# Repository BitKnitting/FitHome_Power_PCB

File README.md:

Kicad is used to create the schematic and layout.
# Power PCB
The Power PCB  monitors the voltage and current of a (North American's) home energy lines.  It is the bottom PCB of three PCBs that when combined provide Watt readings and send them over wireless to an mqtt broker.  The other PCBs include:  
* [The meter PCB](https://github.com/BitKnitting/Tisham_PCB_meter_atm90e26).  The meter PCB includes two atm90e26 energy monitor ICs that takes in the analog readings from the power PCB and converts them into DC measurements a microcontroller can read.  
* [The microcontroller PCB](https://github.com/BitKnitting/Tisham_PCB_Feather).  The microcontroller PCB mounts a microcontroller with wifi - like a Feather RFM95 or a wemos D1 (a bit up in the air as of this date - 4/5/2019).  The microcontroller gets the voltage and current readings from the atm90e26's over SPI and then sends them via mqtt.

The three connect together to become the FitHome hardware.

# Thanks to Those That Went Before
This project extends [Tisham Dhar's work on building energy monitors using an atm90e26](https://github.com/whatnick/DIN_Rail_EnergyMonitor).  In particular, [the DIN Rail energy monitor](https://www.crowdsupply.com/whatnick/atm90e26-energy-monitor-kits).  Besides his open source projects, Tisham has been exceptionally helpful and supportive.  Tisham continues to inspire me.  THANK YOU.

Before I took [Chris Gammell's Contextual Electronics course](https://contextualelectronics.com/), I had absolutely no experience with electronics or building PCBs.  Chris is exceptional in so many ways.  THANK YOU.

There is an exceptional community behind [the OpenEnergyMonitor project](https://learn.openenergymonitor.org/).  They not only provide energy monitoring solutions, but are a wealth of knowledge.  THANK YOU.  In particular, thanks to the kindly delivered advice and help from Robert Wall.  THANK YOU, THANK YOU.

# Background Info
 ## Electricity Coming Into Our Homes
 In our North American homes, 120V of electricity comes in through two power lines (L0 and L1).  A third line (N) acts as the reference point (analog ground) for voltage/current measurements.
 
 _Image from [here](https://learn.openenergymonitor.org/electricity-monitoring/ac-power-theory/use-in-north-america)_  

 See the section in the schematic labelled _Incoming 120V_.  
 ### Surges
 The MOVs(Metal Oxide Varistors - RV1, RV2, and RV3 on the schematic) clamp down on the voltage coming in when there are power surges.  Most of the time, voltage in North American homes oscillates from 0 to a peak voltage of 169 volts.  Sometimes this oscillation is disturbed by a spike in voltage caused by a lightning strike or  switching in the power grid:  
   
 # Voltage Sampling
 The Open Energy Monitor project has [great info](https://learn.openenergymonitor.org/electricity-monitoring/voltage-sensing/measuring-voltage-with-an-acac-power-adapter) on the how and the what of voltage sampling.  See the Voltage Sampling section of the schematic.

 Four resistors are run in series to ensure if any one of the resistors breaks down, the full 120V won’t be sent to the rest of the circuit.  Also, the resistors are rated to handle the incoming voltage (in my case 120V…but to be safe probably 240V rated resistors are a better thing to use). 
 
Noted in the atm90e26's datasheet: The pins that are for voltage sampling (15 and 16): _…are differential inputs for voltage. Input range is 120μVrms~600mVrms…_ 

Looking at the voltage divider formula:
  
```
R1 = 220K * 4 = 880K
R2 = 1K
Vin = 120V
Vout = 120(1/881)= 136mV.  
```  
# DC Power 
The atm90e26's and the microcontrollers need 3.3V DC power to work.  Since we have 120V coming in, we can transform it to provide the 3.3V DC power.  See the 120VAC -> 5 and 3.3VDC section in the schematic.  There are three pieces to the conversion:  
* The 120VAC -> 5VDC [SMPS](https://en.wikipedia.org/wiki/Switched-mode_power_supply).  
* The two LDOs.  The signal coming out of the SMPS is too noisy.  The LDOs clean up the signal.  
* The DC-DC isolator. This isolates the power for the atm90e26s from the power for the microcontroller.
# Current Sampling
See the Current Sampling section of the Kicad schematic.
## Current Transformers
 Two Current Transformers (CTs) are needed to get current readings on the two 120V lines.   
   
 ### SCT-013-000 CT
  This CT is the [YHDC SCT-013-000 Current Transformer](https://learn.openenergymonitor.org/electricity-monitoring/ct-sensors/yhdc-sct-013-000-ct-sensor-report).  It is popular with DIY home energy monitors.  There are two numbers of interest in the [YHDC SCT-013-000 datasheet](http://statics3.seeedstudio.com/assets/file/bazaar/product/101990029-SCT-013-000-Datasheet.pdf):    
* The diameter of the clamp opening - 13 mm  
* The I(OUT) - 50 mA  
As Robert Wall of [the Open Energy Monitor project](https://openenergymonitor.org/) noted to me _...the manufacturer will tweak the number of secondary turns to give the best accuracy overall.  The ratio of a c.t. is __ALWAYS__ specified as a ratio of two currents, the rated primary current to the corresponding secondary current. So your SCT-013-000 is __100 A : 50 mA__._  
#### TRS 3.5 Jack
 The CTs use a [TRS 3.5mm audio jack](https://www.cui.com/product/resource/sj-352x-smt-series.pdf) as the connector.  The [SCT-013-000 datasheet][YHDC SCT-013-000 datasheet](http://statics3.seeedstudio.com/assets/file/bazaar/product/101990029-SCT-013-000-Datasheet.pdf) shows how the sleeve and tip of the TRS jack are wired.    

Output k is at the tip.  Output l as at the sleeve.

Also note the zener diode.  This is great to have in the circuit to prevent deadly voltage when the CT is clamped to a live line but the jack is not plugged into the rest of the circuit containing the burden resistor.
#### Tea Kettle Example
_PLEASE NOTE: Most people would advise against do this.  The clamp exposes an open current source.  Thanks to the zener diode, this is not as dangerous as it seems.  That is assuming there really IS a zener diode and it is working..._  

To clarify the workings of this CT, I measured the current used by our tea kettle.    
  
I plugged the kettle into my power cord extender that I made to separate out the live line of the power cord so that I could clamp on the CT.  The black probe of the DMM is touching the sleeve of the CT's jack.  The red probe is touching the tip.  Setting the DMM to measure AC mA, I get a reading of 5.9mA.  
```
V = 120V
I = 5.9mA * 100A / 50mA = .0059*100/.05 = 11.8A
P = IV = 11.8 * 120 = 1,416w
```
Ah!  The power of the tea kettle!  More like it takes alot of energy to boil water for tea.

## Clamping On 
   
 One CT is clamped onto the L0 line.  The other is clamped onto the L1 line.  Because the CT clamps onto the line, you might hear a CT refered to as a current clamp.  

 ## Characteristics of the CT
 The characteristics of a CT to be considered when sourcing include:
 * The amount of Amp Service.  [From this article _Understanding Your Home's Electrical Load_](https://www.bhg.com/home-improvement/electrical/how-to-check-your-homes-electrical-capacity/) _Different homes need different amp services. A 60-amp service is probably inadequate for a modern home. A 100-amp service is good for a home of less than 3,000 square feet that does not have central air-conditioning or electric heat. A home larger than 2,000 square feet that has central air-conditioning or electric heat probably needs a 200-amp service._  According to [Bill Thompson of the Open Energy Monitor Project](https://community.openenergymonitor.org/t/ct-hole-diameter-for-north-america/5149), _US homes built before the late 60s were wired with Copper and typically had 100 Amp service, which used AWG 0 copper...Sometime in the late 60s to early 70s, Copper Service Entrance Wires were replaced by Aluminum. Since Aluminum has more resistance per foot than Copper, the equivalent Aluminum wire is two gauges larger than its Copper counterpart. About that same time, 200 Amp service became the norm._  
 * The wire gauge.  The Outside Diameter of the wire gauge determines how large the diameter of the CT clamp must be.  As Bill noted, wires could be copper or aluminum, or copper-clad aluminum.  More aluminum, more current - the wider the diameter.  
   * [100 Amp Service uses 1/0 AWG](https://community.openenergymonitor.org/t/ct-hole-diameter-for-north-america/5149/3) = [12.08 mm](https://lugsdirect.com/Wire_Insulation_Outside_Diameter_Thickness_600V.html).  
   * 200 Amp Service uses (up to?) 2/0 - 4/0 AWG.  [4/0 AWG has an Outside diameter of 16.04mm](https://lugsdirect.com/Wire_Insulation_Outside_Diameter_Thickness_600V.html).  
* Whether the burden resistor is included.  This design assumes the CT __does not__ include the burden resistor.  I.e.: it's output is a current and not a voltage.  
* The ratio of I(in) : I(out)  
* The inclusion of a zener diode.  This is a terrific safety measure to make sure when the CT is clamped on, there is on open current source.

### The Schematics
The image below shows how the wires of the CT map into the TRS and PCB wiring.  

### 200A CT

The YHD SCT-013-000 can't be used on 200 Amp houses.  The clamp diameter of at least 16.04 mm.  And most likely it is better to have a different coil ratio for the secondary coils.

 ## Taking a Current Reading
 I first learned how the current reading circuit worked by reading [this excellent article on the OpenEnergyMonitor's site](https://learn.openenergymonitor.org/electricity-monitoring/ct-sensors/interface-with-arduino).  If you (like myself) are new to this stuff, it is worth a read.  

 The CT used in this design outputs current.  A "burden resistor" is to convert into a Voltage that can be read by the microcontroller.  To accomodate readings using the ADC of the Arduino as discussed in the project, a DC bias circuit of AREF/2 (2.5V) lifts ADC readings to be between 0 and AREF (5V).
 
 The atm90e26 does not need a DC bias circuit.  
 ### Burden Resistor
 Tisham's design uses a 12R burden resistor.  This is to accomodate the atm90e26's 600mV Vrms input limit.  The OpenEnergyMonitor's article noted the current output's Amplitude is .0707A.  Vpp = 0.0707 x 12 = 848mV.  The amplitude is then 424mV.  The Vrms = 424*sqrt(2) = 600mV.
 
 As Tisham noted: _In recent designs I have been splitting the 12R into 6R-6R and grounding the middle for signal symmetry._  This is why two 5.8R resistors are used.  I ran an LTSpice with:  
 *  a sine wave set at 60Hz with an amplitude of 0.0707A (from the OpenEnergyMonitor's Arduino article)
 * .tran 0 .1 0 .1  

 # Connectors
 Getting connectors right has always been difficult for me.  The connectors used in the Power PCB include:  
 ## J1
 This is a plug in Terminal Block.  It connects the 120V power lines to the power PCB.
 The ones made by Phoenix Connect:  
 The male contact - [PN 1759059](https://media.digikey.com/pdf/Data%20Sheets/Phoenix%20Contact%20PDFs/1759059.pdf) is soldered to the power PCB.
 
 The female contact - [PN 1757051](https://media.digikey.com/pdf/Data%20Sheets/Phoenix%20Contact%20PDFs/1757051.pdf) plugs into the male contact and screws the wires into one of the 6 positions.  

 The prices for one of these connectors was WAY TOO HIGH. It appears there is a "clone" version that costs far less but is basically the same thing as the ones made by Phoenix Connect.  From an Alibaba quote:  
 ```
 1757051------MX2EDGK-5.08-6P-14------100PCS------0.36USD/PCS 
 1759059------MX2EDGR-5.08-6P-14------100PCS------0.12USD/PCS 
 ```
 ###  MX2EDGR-5.08-6P  
 This is the 6 position male piece.  The pins are at a right angle to the rest of the connection.  I noticed some vendors used MX2EDGRC (i.e.: added a C to the end).
 ###  MX2EDGK-5.08-6P  
 This is the female part that connects into the male part.  It has the screw downs for the power lines (like those in a power cord).
 I noticed the quote used different part numbers:
 ```
 MX2EDGK-5.08-6P-14  

 MX2EDGR-5.08-6P-14  
 ```
 #### First Order
These say they meet an Amp amount of 15A.   I ended up ordering 10 for a female/male at about $1.60 each.  Clearly this can come down significantly.  Right now, in prototype, we're fine with [the ones ordered on newegg](https://www.newegg.com/Product/Product.aspx?Item=9SIAHBU8RD2627).  
   
 __OOPS!__ The male pieces are not at right angles.  I need to be more careful and order by part number.
 __TBD:__ Not ordering any more at this point.  Query Alibaba.com for MX2EDGR.
 
 ## U1 and U2
 These are [the female 3.5 TRS audio part (SJ-3523-SMT-TR)](https://www.cui.com/product/resource/sj-352x-smt-series.pdf). The male audio jack on the end of each current clamp is inserted.
   
 ## J2
 The pin out for the [36 position female PCI Express connector](https://www.amphenol-icc.com/media/wysiwyg/files/drawing/10018784.pdf) that connects the meter PCB to the power PCB.  
 .

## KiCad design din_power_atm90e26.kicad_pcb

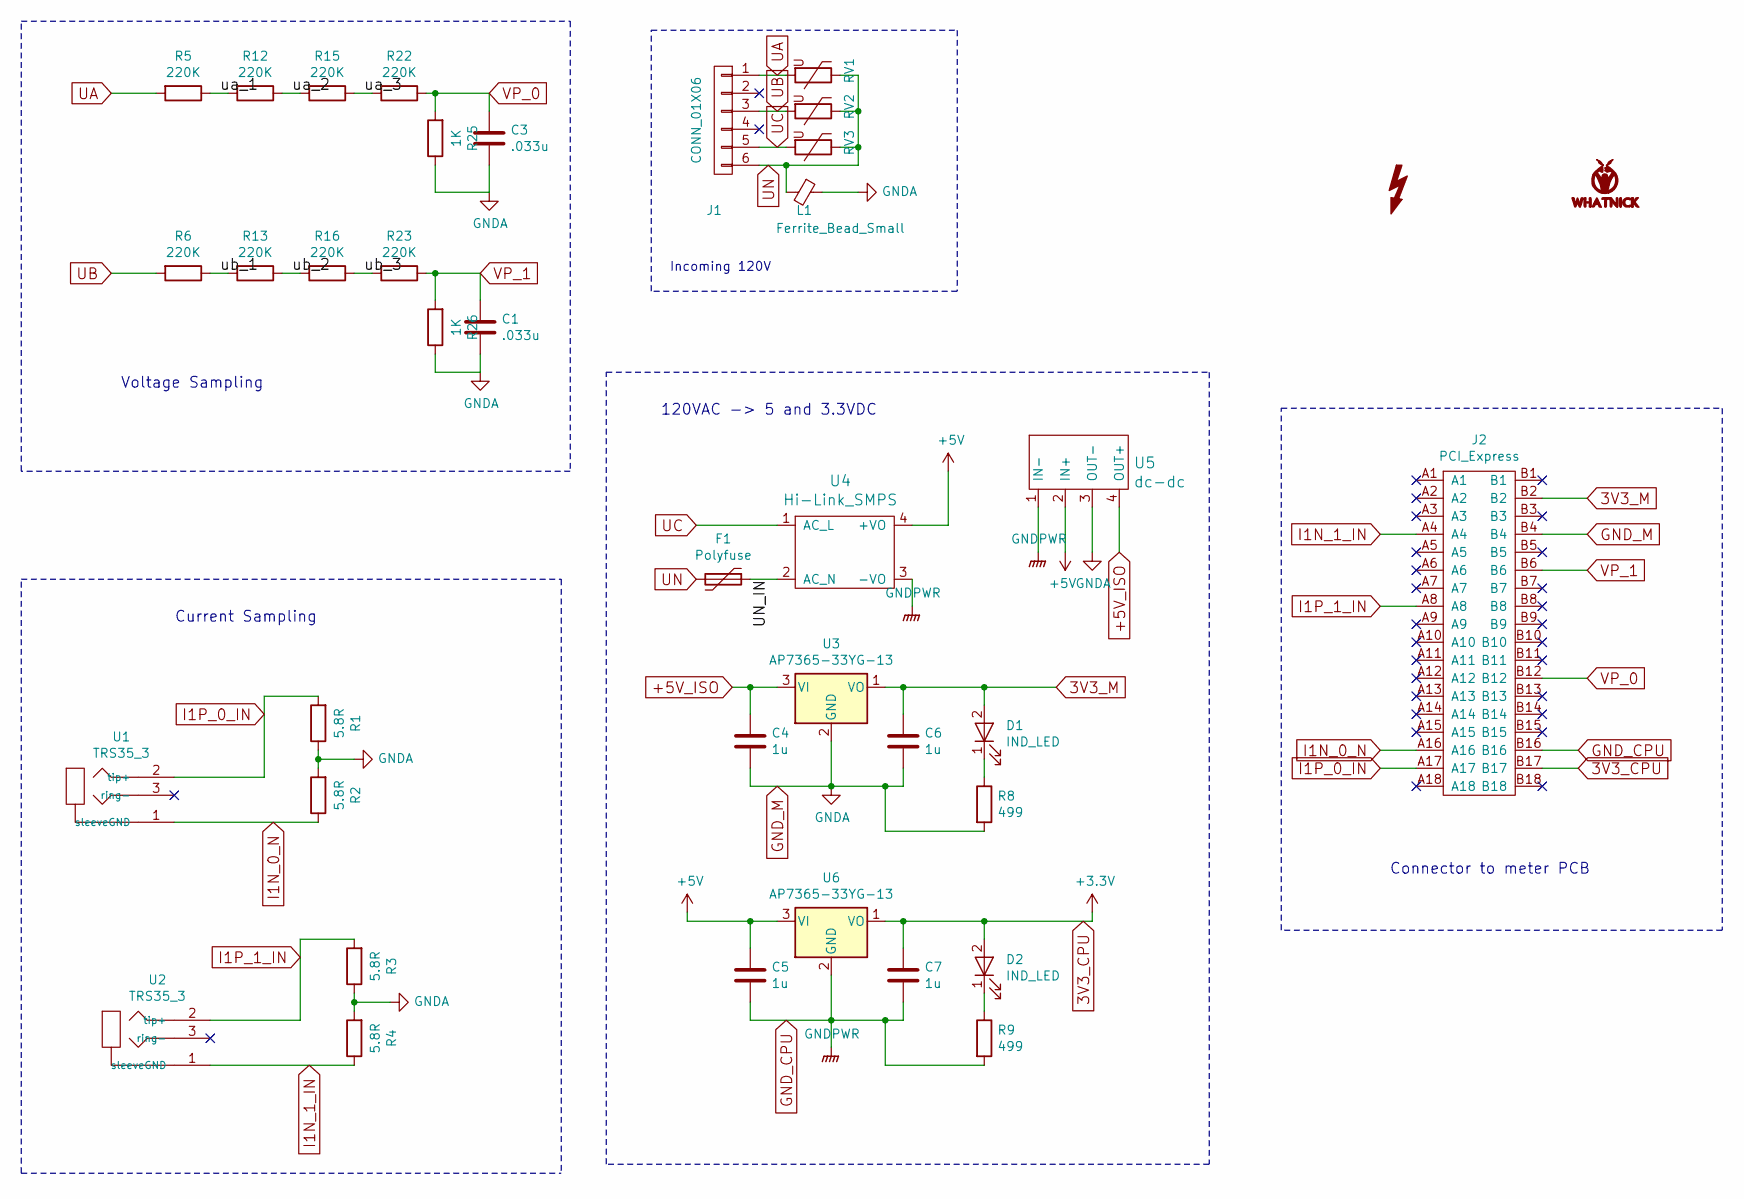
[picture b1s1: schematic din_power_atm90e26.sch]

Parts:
C1, C3: .033u; C_0805_2012Metric
C4, C5, C6, C7: 1u; C_0805_2012Metric
D1, D2: IND_LED; C_0805_2012Metric
F1: Polyfuse; C_Disc_D10.5mm_W5.0mm_P5.00mm
G1: LOGO; Whatnick_logo
J1: CONN_01X06; PhoenixContact_MC-G_06x5.08mm_Angled
J2: PCI_Express; PCIE-36-SKT
L1: Ferrite_Bead_Small; L_1206_3216Metric
R1, R2, R3, R4: 5.8R; R_0603_1608Metric
R5, R6, R12, R13, R15, R16, R22, R23: 220K; R_1206_3216Metric
R8, R9: 499; R_0805_2012Metric
R25, R26: 1K; R_0805_2012Metric
RV1, RV2, RV3: Varistor; SMD-4032
SYM1: SYM_Flash_Small; Fsilk_HV
U1, U2: TRS35_3; Audio-Jack
U3, U6: AP7365-33YG-13; SOT-89-3
U4: Hi-Link_SMPS; HKLPM01
U5: dc-dc; SIP4

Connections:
3V3_CPU: C7.1, D2.2 (A), J2.B17, U6.1 (VO)
3V3_M: C6.1, D1.2 (A), J2.B2, U3.1 (VO)
+5V: C5.1, U4.4 (+VO), U5.2 (IN+), U6.3 (VI)
+5V_ISO: C4.1, U3.3 (VI), U5.4 (OUT+)
/UN_IN: F1.1, U4.2 (AC_N)
/ua_1: R5.1, R12.2
/ua_2: R12.1, R15.2
/ua_3: R15.1, R22.2
/ub_1: R6.1, R13.2
/ub_2: R13.1, R16.2
/ub_3: R16.1, R23.2
GND_CPU: C5.2, C7.2, J2.B16, R9.2, U4.3 (-VO), U5.1 (IN-), U6.2 (GND)
GND_M: C1.2, C3.2, C4.2, C6.2, J2.B4, L1.1, R1.1, R2.2, R3.1, R4.2, R8.2, R25.1, R26.1, U3.2 (GND), U5.3 (OUT-)
I1N_0_N: J2.A16, R2.1, U1.1 (sleeveGND)
I1N_1_IN: J2.A4, R4.1, U2.1 (sleeveGND)
I1P_0_IN: J2.A17, R1.2, U1.2 (tip+)
I1P_1_IN: J2.A8, R3.2, U2.2 (tip+)
unnamed: D1.1 (K), R8.1
unnamed: D2.1 (K), R9.1
UA: J1.1, R5.2, RV1.2
UB: J1.3, R6.2, RV2.2
UC: J1.5, RV3.2, U4.1 (AC_L)
UN: F1.2, J1.6, L1.2, RV1.1, RV2.1, RV3.1
VP_0: C3.1, J2.B12, R22.1, R25.2
VP_1: C1.1, J2.B6, R23.1, R26.2

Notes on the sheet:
120VAC -> 5 and 3.3VDC
Voltage Sampling
Current Sampling
Connector to meter PCB
Incoming 120V

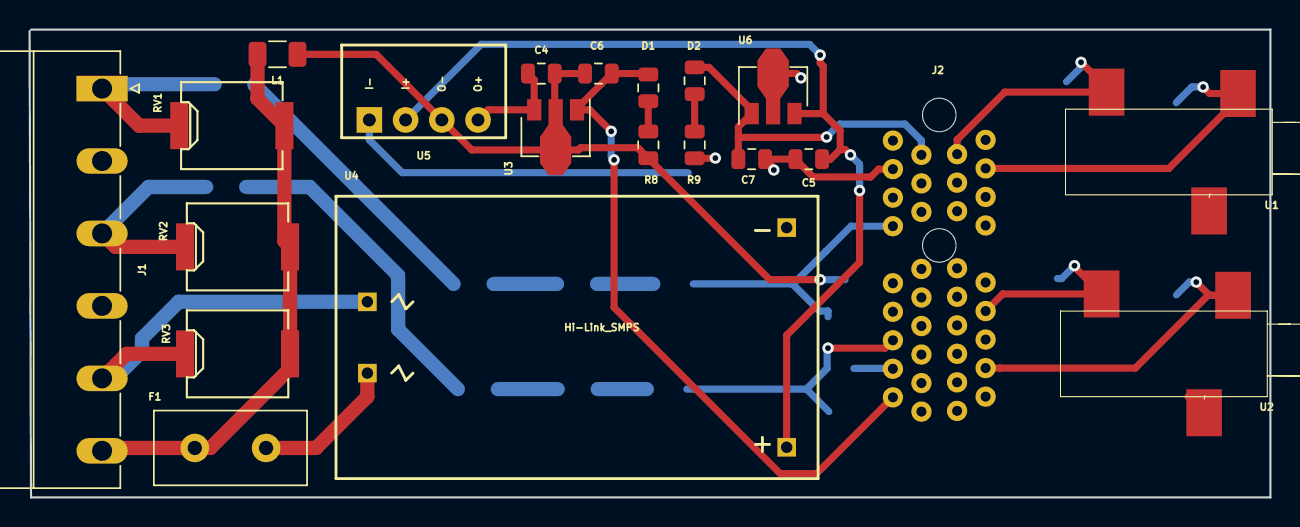
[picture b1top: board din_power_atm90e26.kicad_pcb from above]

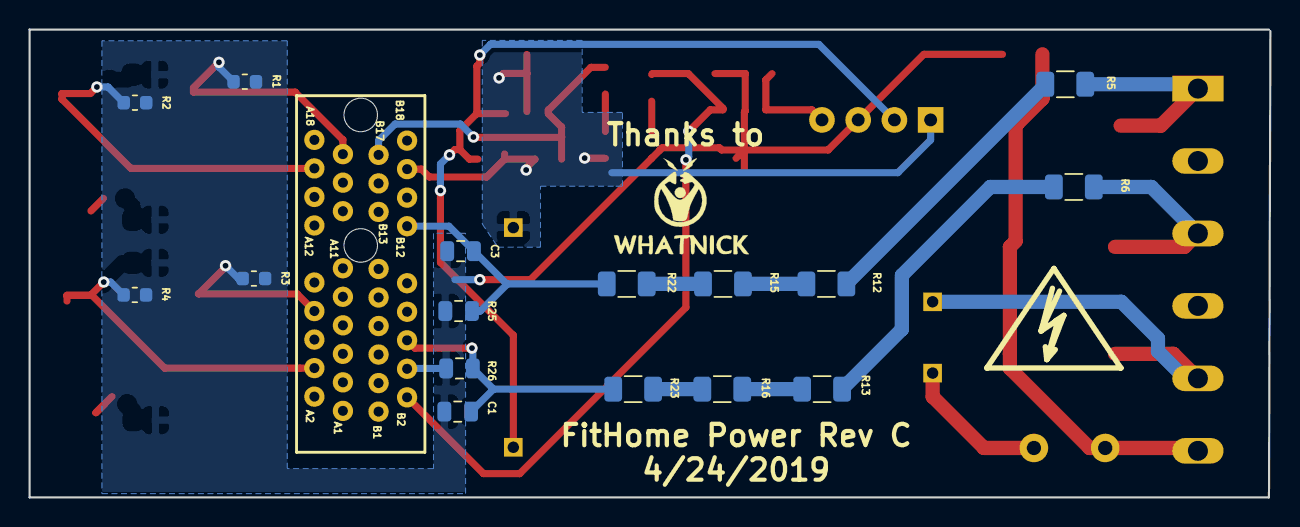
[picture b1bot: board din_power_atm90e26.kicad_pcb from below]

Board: 2 copper layers, 87.0 x 32.8 mm, 39 parts (18 on the bottom side), 25 nets.

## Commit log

2019-03-16 added image
2019-03-16 updated readme.
2019-03-17 added image and updated readme
2019-03-17 updated readme with image.
2019-03-18 minor updates.
2019-03-23 First pass at layout matching meter PCB
2019-04-04 Updated PCI Express connector (v. B)
2019-04-05 Evolved readme.
2019-04-08 updated schematic after changing dir name.
2019-04-08 OSH Park Rev B
2019-04-16 update readme.
2019-04-23 Updates as build Power PCB Rev B.
2019-05-08 minor correction in Readme.
2019-07-07 Updated posts.
